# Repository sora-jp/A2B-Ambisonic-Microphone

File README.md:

# Passive Sonar / Ambisonic Microphone
This repo contains a design for a working ambisonic microphone, based on AD2427W A2B transcievers, along with Infineon IM73D122V01XTMA1 MEMS microphones.

## Structure
- kicad_micboard/ : Design files for the microphone board (firmware supports up to 16 of these)
- kicad_iface/ : Design files for the MCHStreamer interface board (only one of these needed)
- firmware_iface/ : Firmware for the MCHStreamer interface board

These folders each contain a README.md, describing their contents in more detail, along with an ORDERING.md giving details on how to order each board.

## Cabling
The cables between nodes are **straight-through twisted pair 2-pin JST-PH** cables. I crimped these cables myself, but you could easily order single-ended pre-crimped cables and then twist and solder them manually

## Known issues
- The voltage given to the interface board dictates how many nodes you can connect in series. For 5 volts, it can only support 6 nodes. For 15 nodes, you need to power the interface board with between 8V and 9V. It will *probably* work on 10V, but won't work on 12V. Some cheap 9V power supplies output *way* more than 9V when unloaded, so be careful with what power supply you choose.
- The A2B transciever on the interface board is missing connections for the I2C address lines. In theory, the actual I2C address of the transciever is undefined, in practice it works. If it doesn't, change the I2C address in the firmware.

## Future work
- The microphone boards have an expansion port, allowing the system to support up to 32 microphones (in theory, this hasn't been tested). The daughter-board to connect to said port hasn't been designed yet.
- The firmware is still very early, and doesn't correctly handle every edgecase. Ideally it should do line-fault diagnostics, but this is currently not implemented.

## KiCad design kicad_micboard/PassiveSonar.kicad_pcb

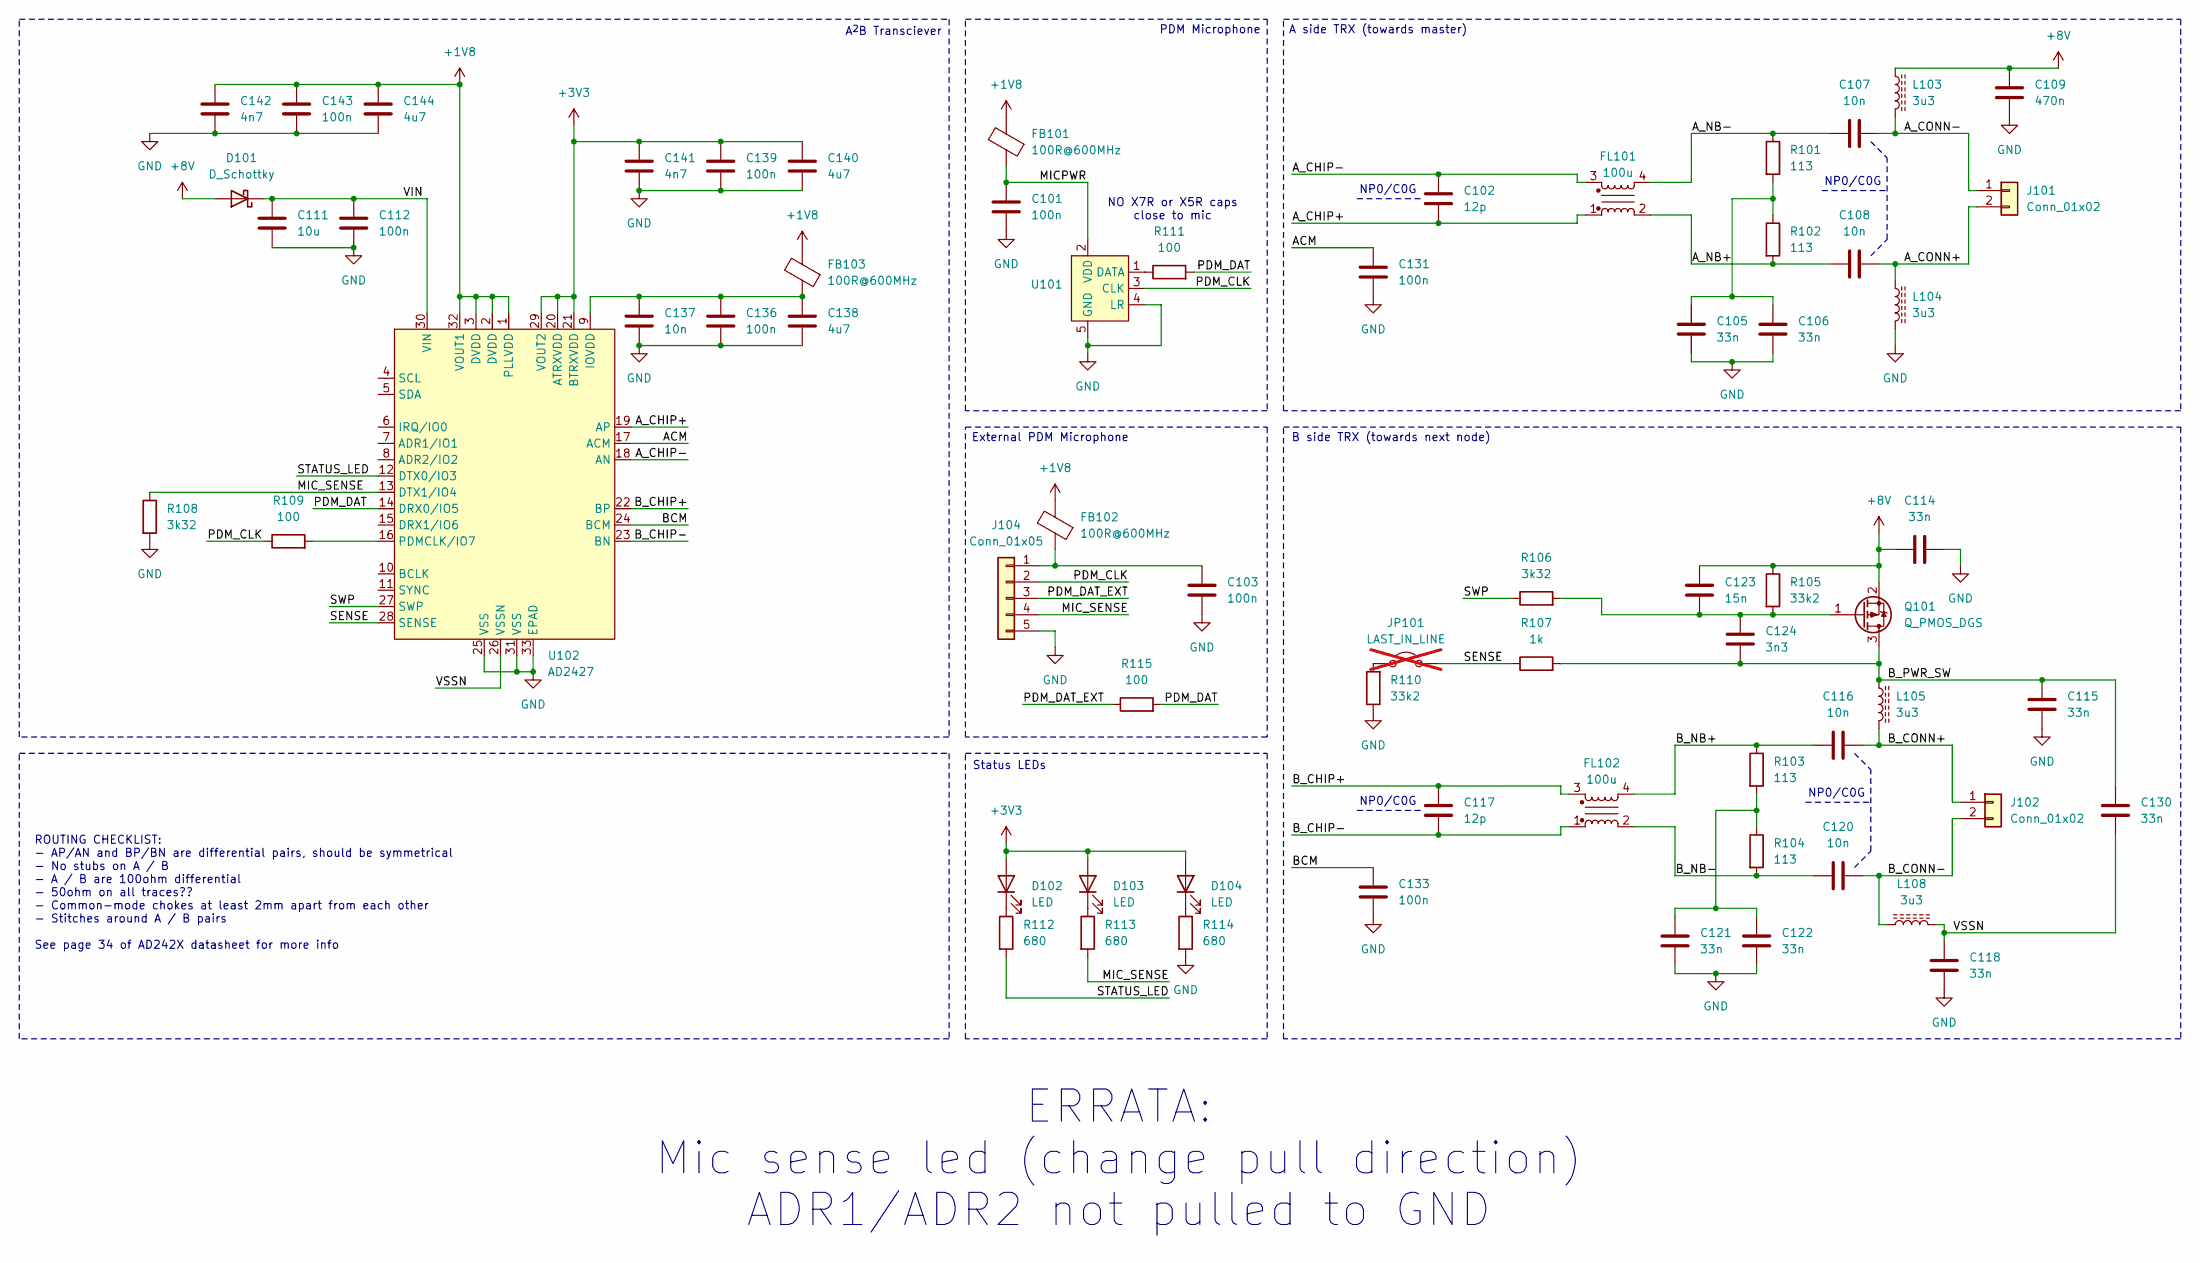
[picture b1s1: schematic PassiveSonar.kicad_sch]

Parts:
C101, C103, C112, C131, C133, C136, C139, C143: 100n; C_0402_1005Metric; JLC 0402
C102, C117: 12p; C_0402_1005Metric; JLC 0402
C105, C106, C114, C115, C118, C121, C122, C130: 33n; C_0603_1608Metric; JLC 0603
C107, C108, C116, C120, C137: 10n; C_0402_1005Metric; JLC 0402
C109: 470n; C_0805_2012Metric; JLC 0805
C111: 10u; C_0805_2012Metric; JLC 0805
C123: 15n; C_0603_1608Metric; JLC 0603
C124: 3n3; C_0402_1005Metric; JLC 0402
C138, C140, C144: 4u7; C_0603_1608Metric; JLC 0603
C141, C142: 4n7; C_0402_1005Metric; JLC 0402
D101: D_Schottky; D_SMA; JLC SMA(DO-214AC)
D102, D103, D104: LED; LED_0603_1608Metric; JLC 0603
FB101, FB102, FB103: 100R@600MHz; R_0603_1608Metric; JLC 0603
FL101, FL102: 100u; TDK-ACT1210L-101-2P-TL00; JLC SMD,3.9x2.5x2.5mm
J101, J102: Conn_01x02; JST_PH_S2B-PH-SM4-TB_1x02-1MP_P2.00mm_Horizontal; JLC SMD,P=2mm
J104: Conn_01x05; JST_PH_S5B-PH-SM4-TB_1x05-1MP_P2.00mm_Horizontal; JLC SMD
JP101: LAST_IN_LINE; PinHeader_1x02_P1.27mm_Vertical; not fitted
L103, L104, L105, L108: 3u3; L_0805_2012Metric; JLC 0805
Q101: Q_PMOS_DGS; SOT-23; JLC SOT-23
R101, R102, R103, R104: 113; R_0603_1608Metric; JLC 0603
R105, R110: 33k2; R_0402_1005Metric; JLC 0402
R106, R108: 3k32; R_0402_1005Metric; JLC 0402
R107: 1k; R_0402_1005Metric; JLC 0402
R109, R111, R115: 100; R_0402_1005Metric; JLC 0402
R112, R113, R114: 680; R_0402_1005Metric; JLC 0402
U101: Infineon_PG-LLGA-5-1; JLC SMD
U102: AD2427; LFCSP-32-1EP_5x5mm_P0.5mm_EP3.5x3.5mm; JLC LFCSP-32-SS(5x5)

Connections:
+1V8: C142.1, C143.1, C144.1, FB101.2, FB102.2, FB103.2, U102.1 (PLLVDD), U102.2 (DVDD), U102.3 (DVDD), U102.32 (VOUT1)
+3V3: C139.1, C140.1, C141.1, D102.2 (A), D103.2 (A), D104.2 (A), U102.20 (ATRXVDD), U102.21 (BTRXVDD), U102.29 (VOUT2)
+8V: C109.1, C114.1, C123.1, D101.2 (A), L103.1, Q101.2 (S), R105.1
/ACM: C131.1, U102.17 (ACM)
/A_CHIP+: C102.1, FL101.1, U102.19 (AP)
/A_CHIP-: C102.2, FL101.3, U102.18 (AN)
/A_CONN+: C108.1, J101.2, L104.1
/A_CONN-: C107.1, J101.1, L103.2
/A_NB+: C108.2, FL101.2, R102.2
/A_NB-: C107.2, FL101.4, R101.1
/BCM: C133.1, U102.24 (BCM)
/B_CHIP+: C117.2, FL102.3, U102.22 (BP)
/B_CHIP-: C117.1, FL102.1, U102.23 (BN)
/B_CONN+: C116.1, J102.1, L105.2
/B_CONN-: C120.1, J102.2, L108.1
/B_NB+: C116.2, FL102.4, R103.1
/B_NB-: C120.2, FL102.2, R104.2
/B_PWR_SW: C115.1, C124.2, C130.1, L105.1, Q101.3 (D), R107.2
/MICPWR: C101.2, FB101.1, U101.2 (VDD)
/MIC_SENSE: J104.4, R108.1, R113.2, U102.13 (DTX1/IO4)
/PDM_CLK: J104.2, R109.1, U101.3 (CLK)
/PDM_DAT: R111.2, R115.2, U102.14 (DRX0/IO5)
/PDM_DAT_EXT: J104.3, R115.1
/SENSE: JP101.2 (B), R107.1, U102.28 (SENSE)
/STATUS_LED: R112.2, U102.12 (DTX0/IO3)
/SWP: R106.1, U102.27 (SWP)
/VIN: C111.1, C112.1, D101.1 (K), U102.30 (VIN)
/VSSN: C118.1, C130.2, L108.2, U102.26 (VSSN)
GND: C101.1, C103.1, C105.1, C106.1, C109.2, C111.2, C112.2, C114.2, C115.2, C118.2, C121.1, C122.1, C131.2, C133.2, C136.2, C137.2, C138.2, C139.2, C140.2, C141.2, C142.2, C143.2, C144.2, J104.5, L104.2, R108.2, R110.1, R114.2, U101.4 (LR), U101.5 (GND), U102.25 (VSS), U102.31 (VSS), U102.33 (EPAD)
unnamed: C105.2, C106.2, R101.2, R102.1
unnamed: C121.2, C122.2, R103.2, R104.1
unnamed: D102.1 (K), R112.1
unnamed: D103.1 (K), R113.1
unnamed: D104.1 (K), R114.1
unnamed: C103.2, FB102.1, J104.1
unnamed: JP101.1 (A), R110.2
unnamed: C123.2, C124.1, Q101.1 (G), R105.2, R106.2
unnamed: R111.1, U101.1 (DATA)
unnamed: C136.1, C137.1, C138.1, FB103.1, U102.9 (IOVDD)
unnamed: R109.2, U102.16 (PDMCLK/IO7)

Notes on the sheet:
B side TRX (towards next node)
Status LEDs
ROUTING CHECKLIST: - AP/AN and BP/BN are differential pairs, should be symmetrical - No stubs on A / B - A / B are 100ohm differential - 50ohm on all traces?? - Common-mode chokes at least 2mm apart from each other - Stitches around A / B pairs See page 34 of AD242X datasheet for more info
NP0/C0G
A^{2}B Transciever
A side TRX (towards master)
PDM Microphone
NO X7R or X5R caps close to mic
External PDM Microphone
ERRATA: Mic sense led (change pull direction) ADR1/ADR2 not pulled to GND

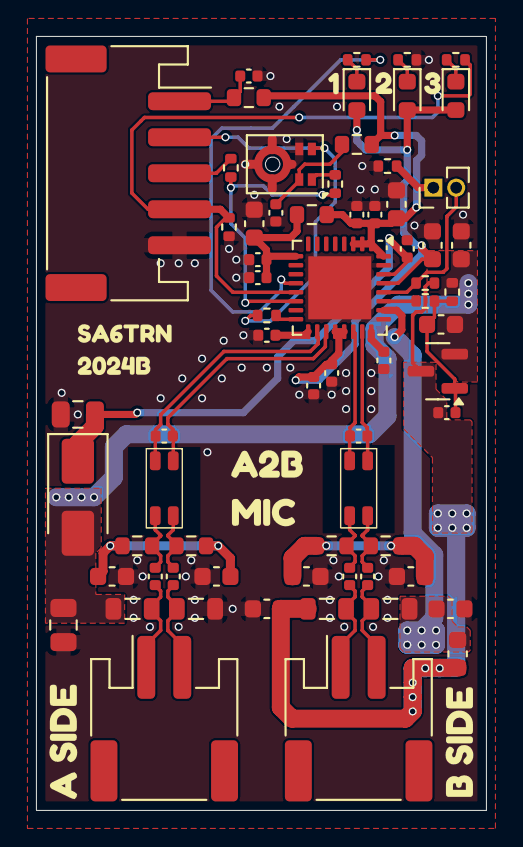
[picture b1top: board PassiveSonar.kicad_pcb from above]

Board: 4 copper layers, 25.0 x 43.0 mm, 74 parts (0 on the bottom side), 40 nets.

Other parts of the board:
kibuzzard-66BA53B9: G***; kibuzzard-66BA53B9
kibuzzard-66BA534A: G***; kibuzzard-66BA534A
kibuzzard-66BA542A: G***; kibuzzard-66BA542A
kibuzzard-66BA5330: G***; kibuzzard-66BA5330
kibuzzard-66BA5382: G***; kibuzzard-66BA5382
kibuzzard-66BA5389: G***; kibuzzard-66BA5389
kibuzzard-66BA5390: G***; kibuzzard-66BA5390

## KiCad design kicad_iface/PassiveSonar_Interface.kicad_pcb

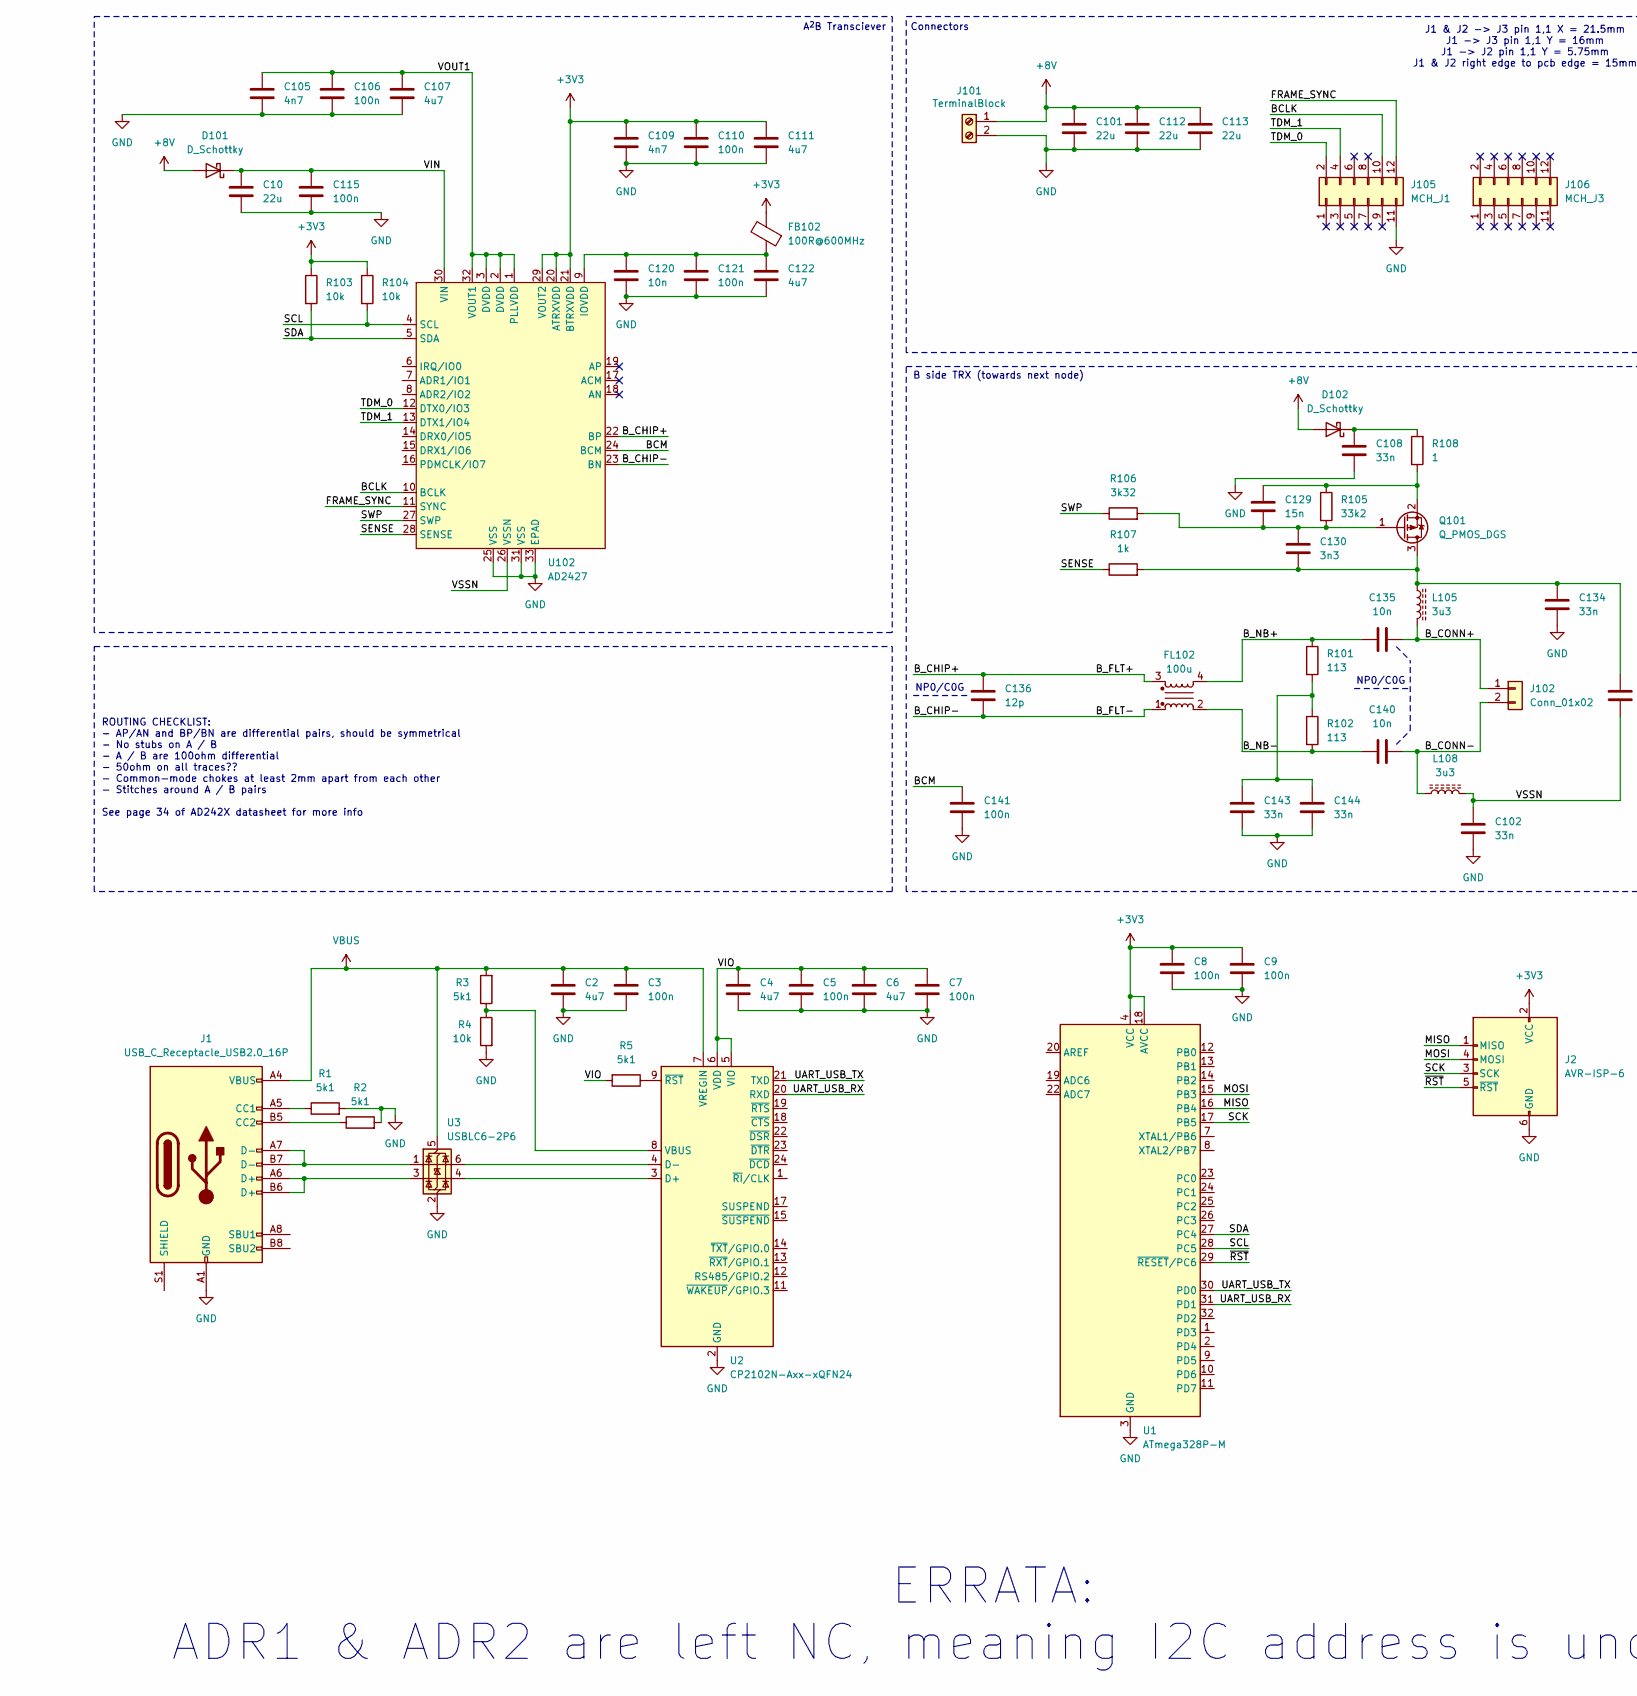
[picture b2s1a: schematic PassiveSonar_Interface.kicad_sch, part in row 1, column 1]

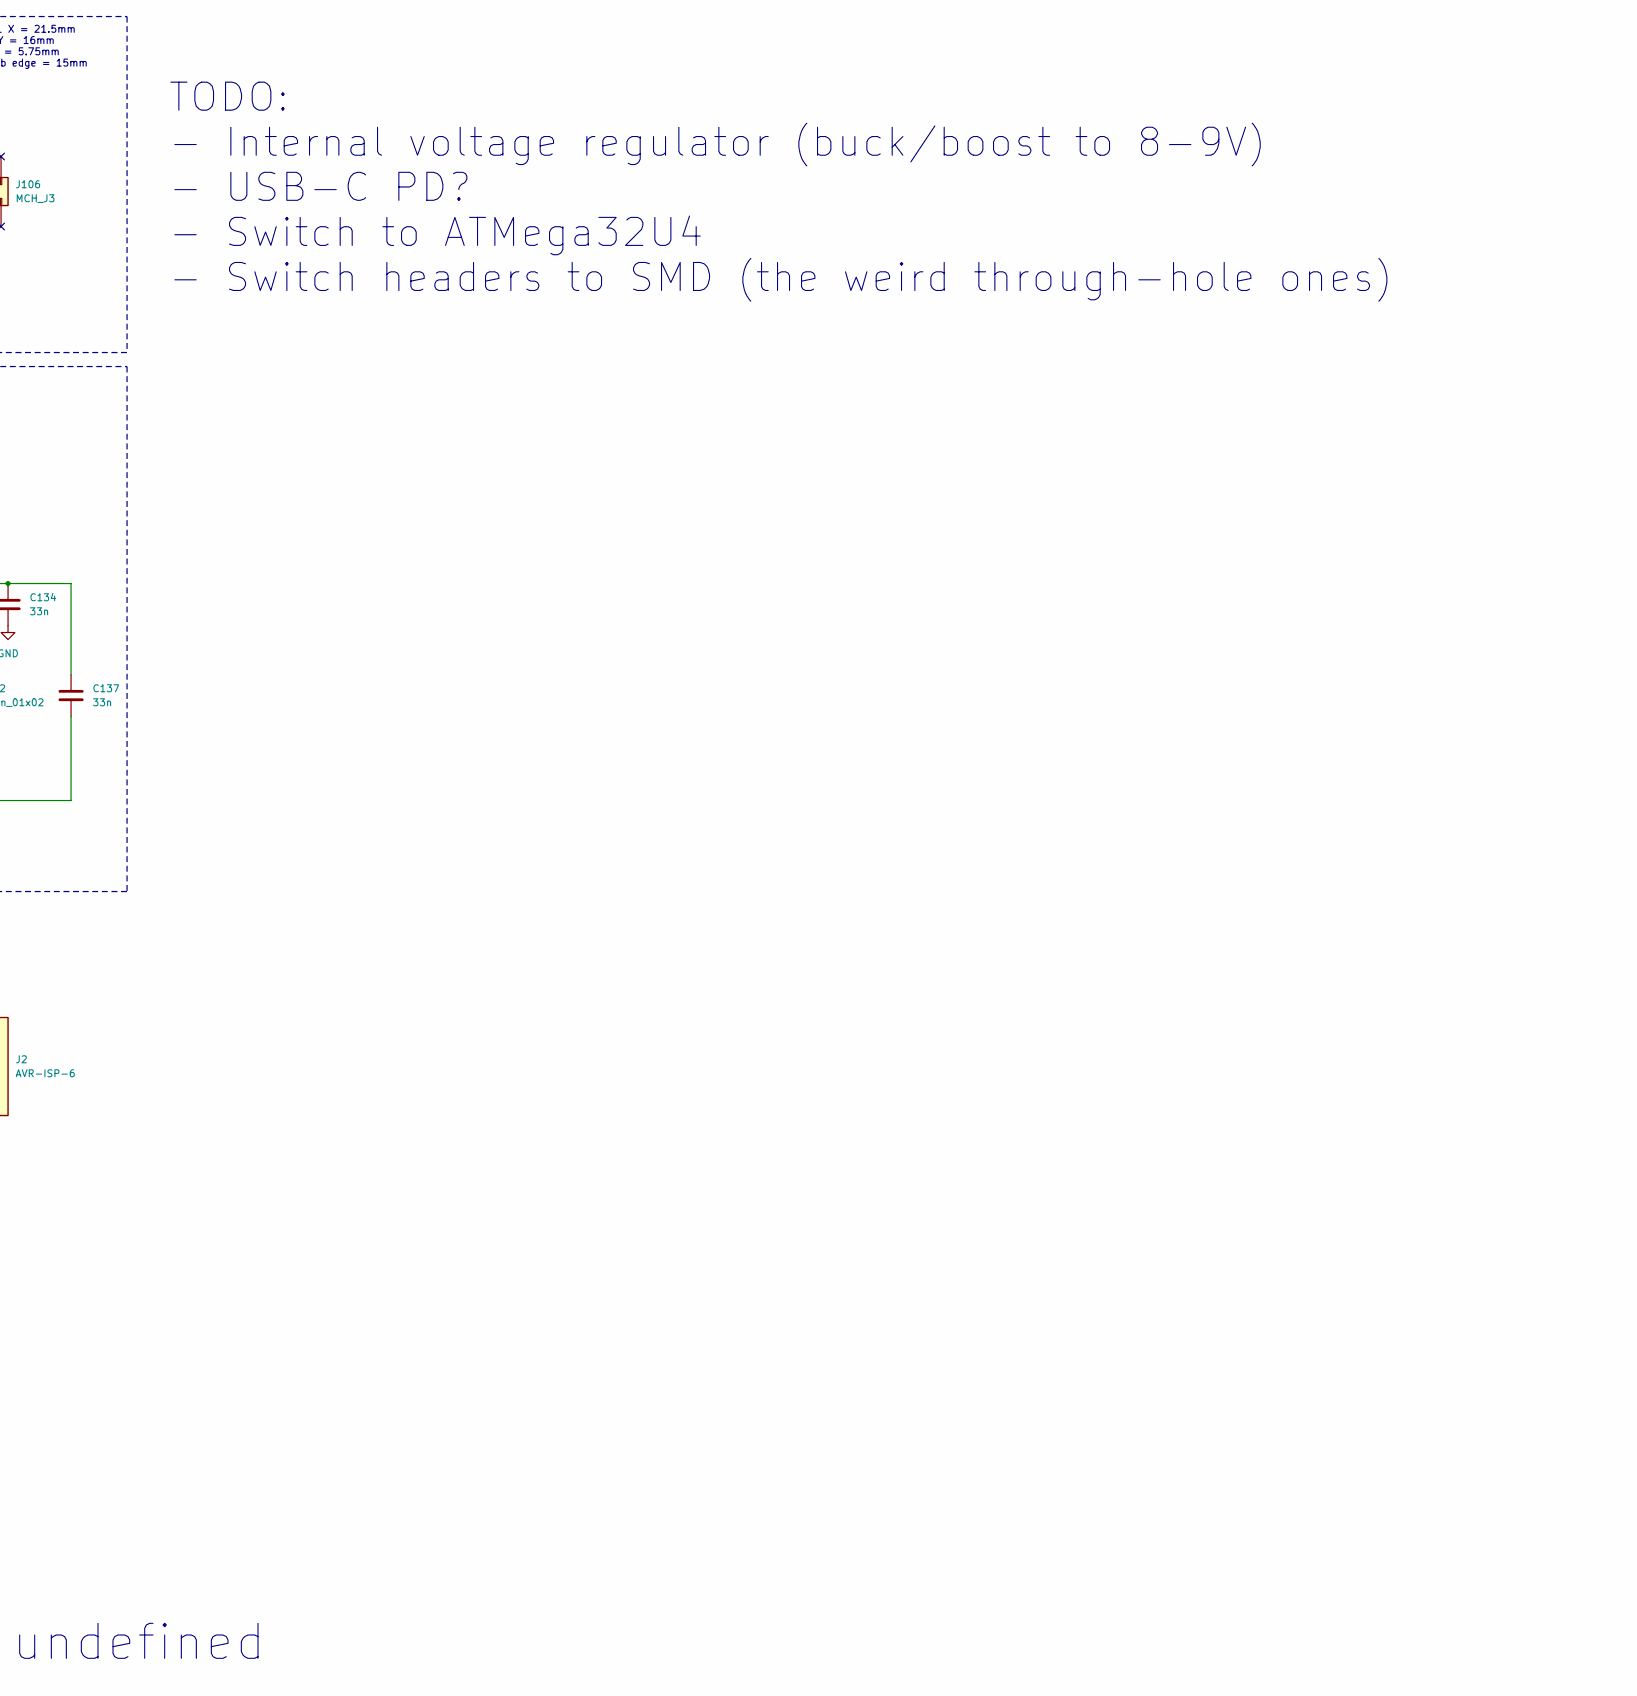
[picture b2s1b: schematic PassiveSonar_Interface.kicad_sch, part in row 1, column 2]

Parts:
C2, C4, C6, C107, C111, C122: 4u7; C_0603_1608Metric; JLC 0603
C3, C5, C7, C8, C9, C106, C110, C115, C121, C141: 100n; C_0402_1005Metric; JLC 0402
C10, C101, C112, C113: 22u; C_0805_2012Metric; JLC 0805
C102, C108, C134, C137, C143, C144: 33n; C_0603_1608Metric; JLC 0603
C105, C109: 4n7; C_0402_1005Metric; JLC 0402
C120, C135, C140: 10n; C_0402_1005Metric; JLC 0402
C129: 15n; C_0603_1608Metric; JLC 0603
C130: 3n3; C_0402_1005Metric; JLC 0402
C136: 12p; C_0402_1005Metric; JLC 0402
D101, D102: D_Schottky; D_SMA; JLC SMA(DO-214AC)
FB102: 100R@600MHz; R_0603_1608Metric; JLC 0603
FL102: 100u; TDK-ACT1210L-101-2P-TL00; JLC SMD,3.9x2.5x2.5mm
J1: USB_C_Receptacle_USB2.0_16P; USB_C_Receptacle_HRO_TYPE-C-31-M-12; JLC SMD
J2: AVR-ISP-6; PinHeader_2x03_P2.54mm_Vertical_SMD; LCSC C124390
J101: TerminalBlock; TerminalBlock_Phoenix_MKDS-1,5-2_1x02_P5.00mm_Horizontal
J102: Conn_01x02; JST_PH_S2B-PH-SM4-TB_1x02-1MP_P2.00mm_Horizontal; JLC SMD,P=2mm
J105: MCH_J1; PinSocket_2x06_P2.00mm_Vertical; Mouser 872631223
J106: MCH_J3; PinSocket_2x06_P2.00mm_Vertical; Mouser 872631223
L105, L108: 3u3; L_0805_2012Metric; JLC 0805
Q101: Q_PMOS_DGS; SOT-23; JLC SOT-23
R1, R2, R3, R5: 5k1; R_0402_1005Metric; JLC 0402
R4, R103, R104: 10k; R_0402_1005Metric; JLC 0402
R101, R102: 113; R_0603_1608Metric; JLC 0603
R105: 33k2; R_0402_1005Metric; JLC 0402
R106: 3k32; R_0402_1005Metric; JLC 0402
R107: 1k; R_0402_1005Metric; JLC 0402
R108: 1; R_1206_3216Metric; JLC 1206
U1: ATmega328P-M; QFN-32-1EP_5x5mm_P0.5mm_EP3.1x3.1mm; JLC VQFN-32(5x5)
U2: CP2102N-Axx-xQFN24; QFN-24-1EP_4x4mm_P0.5mm_EP2.6x2.6mm; JLC QFN-24-EP(4x4)
U3: USBLC6-2P6; SOT-666; JLC SOT-666-6
U102: AD2427; LFCSP-32-1EP_5x5mm_P0.5mm_EP3.5x3.5mm; JLC LFCSP-32-SS(5x5)

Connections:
+3V3: C8.1, C9.1, C109.1, C110.1, C111.1, FB102.2, J2.2 (VCC), R103.1, R104.1, U1.4 (VCC), U1.6 (VCC), U1.18 (AVCC), U102.20 (ATRXVDD), U102.21 (BTRXVDD), U102.29 (VOUT2)
+8V: C101.1, C112.1, C113.1, D101.2 (A), D102.2 (A), J101.1
/BCLK: J105.10, U102.10 (BCLK)
/BCM: C141.1, U102.24 (BCM)
/B_CHIP+: C136.2, FL102.3, U102.22 (BP)
/B_CHIP-: C136.1, FL102.1, U102.23 (BN)
/B_CONN+: C135.1, J102.1, L105.2
/B_CONN-: C140.1, J102.2, L108.1
/B_NB+: C135.2, FL102.4, R101.1
/B_NB-: C140.2, FL102.2, R102.2
/FRAME_SYNC: J105.12, U102.11 (SYNC)
/MISO: J2.1 (MISO), U1.16 (PB4)
/MOSI: J2.4 (MOSI), U1.15 (PB3)
/SCK: J2.3 (SCK), U1.17 (PB5)
/SCL: R104.2, U1.28 (PC5), U102.4 (SCL)
/SDA: R103.2, U1.27 (PC4), U102.5 (SDA)
/SENSE: R107.1, U102.28 (SENSE)
/SWP: R106.1, U102.27 (SWP)
/TDM_0: J105.2, U102.12 (DTX0/IO3)
/TDM_1: J105.4, U102.13 (DTX1/IO4)
/UART_USB_RX: U1.31 (PD1), U2.20 (RXD)
/UART_USB_TX: U1.30 (PD0), U2.21 (TXD)
/VIN: C10.1, C115.1, D101.1 (K), U102.30 (VIN)
/VIO: C4.1, C5.1, C6.1, C7.1, R5.2, U2.5 (VIO), U2.6 (VDD)
/VOUT1: C105.1, C106.1, C107.1, U102.1 (PLLVDD), U102.2 (DVDD), U102.3 (DVDD), U102.32 (VOUT1)
/VSSN: C102.1, C137.2, L108.2, U102.26 (VSSN)
/~RST: J2.5 (~RST), U1.29 (~RESET/PC6)
GND: C2.2, C3.2, C4.2, C5.2, C6.2, C7.2, C8.2, C9.2, C10.2, C101.2, C102.2, C105.2, C106.2, C107.2, C108.1, C109.2, C110.2, C111.2, C112.2, C113.2, C115.2, C120.2, C121.2, C122.2, C134.2, C141.2, C143.1, C144.1, J1.A1 (GND), J1.A12 (GND), J1.B1 (GND), J1.B12 (GND), J2.6 (GND), J101.2, J105.11, R1.2, R2.2, R4.2, U1.3 (GND), U1.5 (GND), U1.21 (GND), U1.33 (GND), U2.2 (GND), U2.25 (GND), U3.2 (GND), U102.25 (VSS), U102.31 (VSS), U102.33 (EPAD)
unnamed: C143.2, C144.2, R101.2, R102.1
unnamed: C108.2, D102.1 (K), R108.2
unnamed: J1.A5 (CC1), R1.1
unnamed: J1.B5 (CC2), R2.1
unnamed: J1.A6 (D+), J1.B6 (D+), U3.3 (I/O2)
unnamed: J1.A7 (D-), J1.B7 (D-), U3.1 (I/O1)
unnamed: C130.2, C134.1, C137.1, L105.1, Q101.3 (D), R107.2
unnamed: C129.2, C130.1, Q101.1 (G), R105.2, R106.2
unnamed: C129.1, Q101.2 (S), R105.1, R108.1
unnamed: U2.3 (D+), U3.4 (I/O2)
unnamed: U2.4 (D-), U3.6 (I/O1)
unnamed: R3.1, R4.1, U2.8 (VBUS)
unnamed: R5.1, U2.9 (~RST)
unnamed: C120.1, C121.1, C122.1, FB102.1, U102.9 (IOVDD)
VBUS: C2.1, C3.1, J1.A4 (VBUS), J1.A9 (VBUS), J1.B4 (VBUS), J1.B9 (VBUS), R3.2, U2.7 (VREGIN), U3.5 (VBUS)

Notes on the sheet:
Connectors
ROUTING CHECKLIST: - AP/AN and BP/BN are differential pairs, should be symmetrical - No stubs on A / B - A / B are 100ohm differential - 50ohm on all traces?? - Common-mode chokes at least 2mm apart from each other - Stitches around A / B pairs See page 34 of AD242X datasheet for more info
B side TRX (towards next node)
TODO: - Internal voltage regulator (buck/boost to 8-9V) - USB-C PD? - Switch to ATMega32U4 - Switch headers to SMD (the weird through-hole ones)
A^{2}B Transciever
NP0/C0G
ERRATA: ADR1 & ADR2 are left NC, meaning I2C address is undefined
J1 & J2 -> J3 pin 1,1 X = 21.5mm J1 -> J3 pin 1,1 Y = 16mm J1 -> J2 pin 1,1 Y = 5.75mm J1 & J2 right edge to pcb edge = 15mm

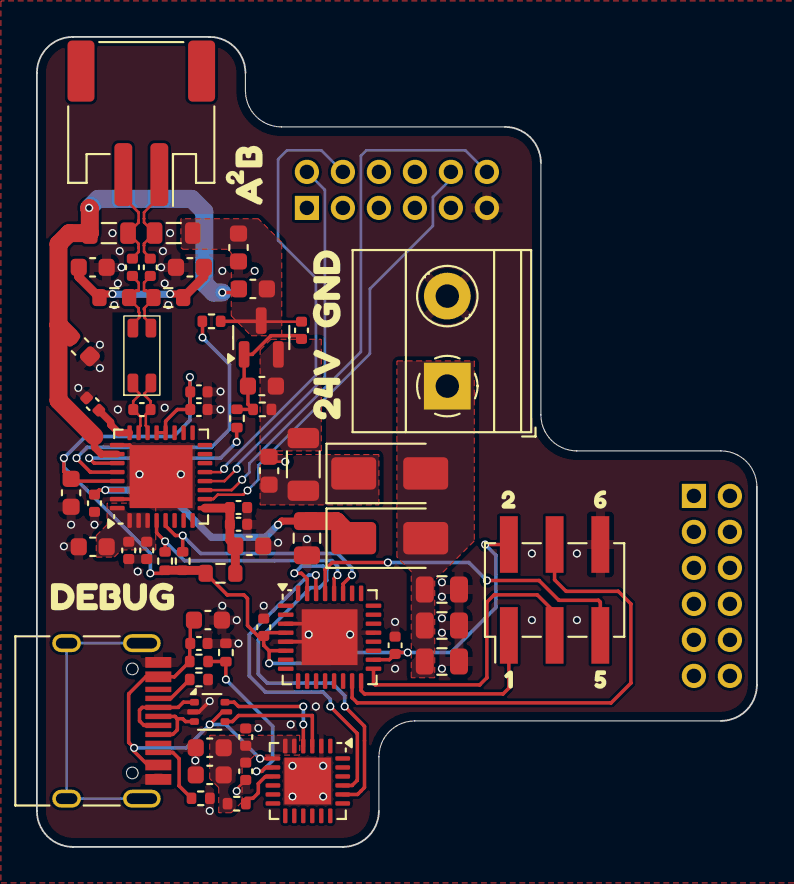
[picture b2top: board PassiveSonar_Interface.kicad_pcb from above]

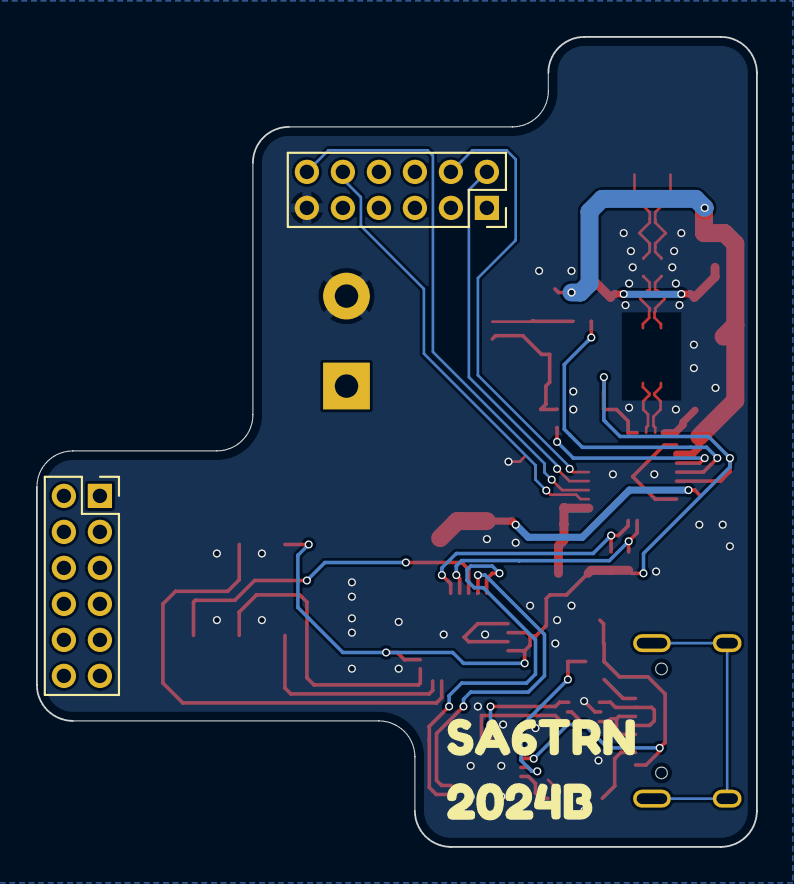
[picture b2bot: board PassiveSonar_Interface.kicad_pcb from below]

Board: 4 copper layers, 40.0 x 45.0 mm, 74 parts (3 on the bottom side), 43 nets.

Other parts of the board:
kibuzzard-66D2F73E: G***; kibuzzard-66D2F73E
kibuzzard-66D2F76B: G***; kibuzzard-66D2F76B
kibuzzard-66D2F77A: G***; kibuzzard-66D2F77A
kibuzzard-66D2F748: G***; kibuzzard-66D2F748
kibuzzard-66D2F788: G***; kibuzzard-66D2F788
kibuzzard-66D2F791: G***; kibuzzard-66D2F791
kibuzzard-66D2F797: G***; kibuzzard-66D2F797
kibuzzard-66D88E33: G***; kibuzzard-66D88E33
kibuzzard-66D3000E: G***; kibuzzard-66D3000E
kibuzzard-66D30007: G***; kibuzzard-66D30007

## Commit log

2024-11-21 Remove unnecessary TODO in README
